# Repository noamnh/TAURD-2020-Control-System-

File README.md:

# TAURD-2020-Control-System
TAU - formula student control system design
this control system include two nucleo micro controllers board which communicate each other via can
and transmit data between section and areas of the formula vehicle.
the main purpose is to transmit the pedal data from the front micro controller to the rear micro controller
the rear micro controller controls the thorttle position.
for making a robust and reliable a pcb board was design and prduced via eagle pcb cad.

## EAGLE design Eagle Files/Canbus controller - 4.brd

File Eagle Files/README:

This is the files of the pcb printed for this project

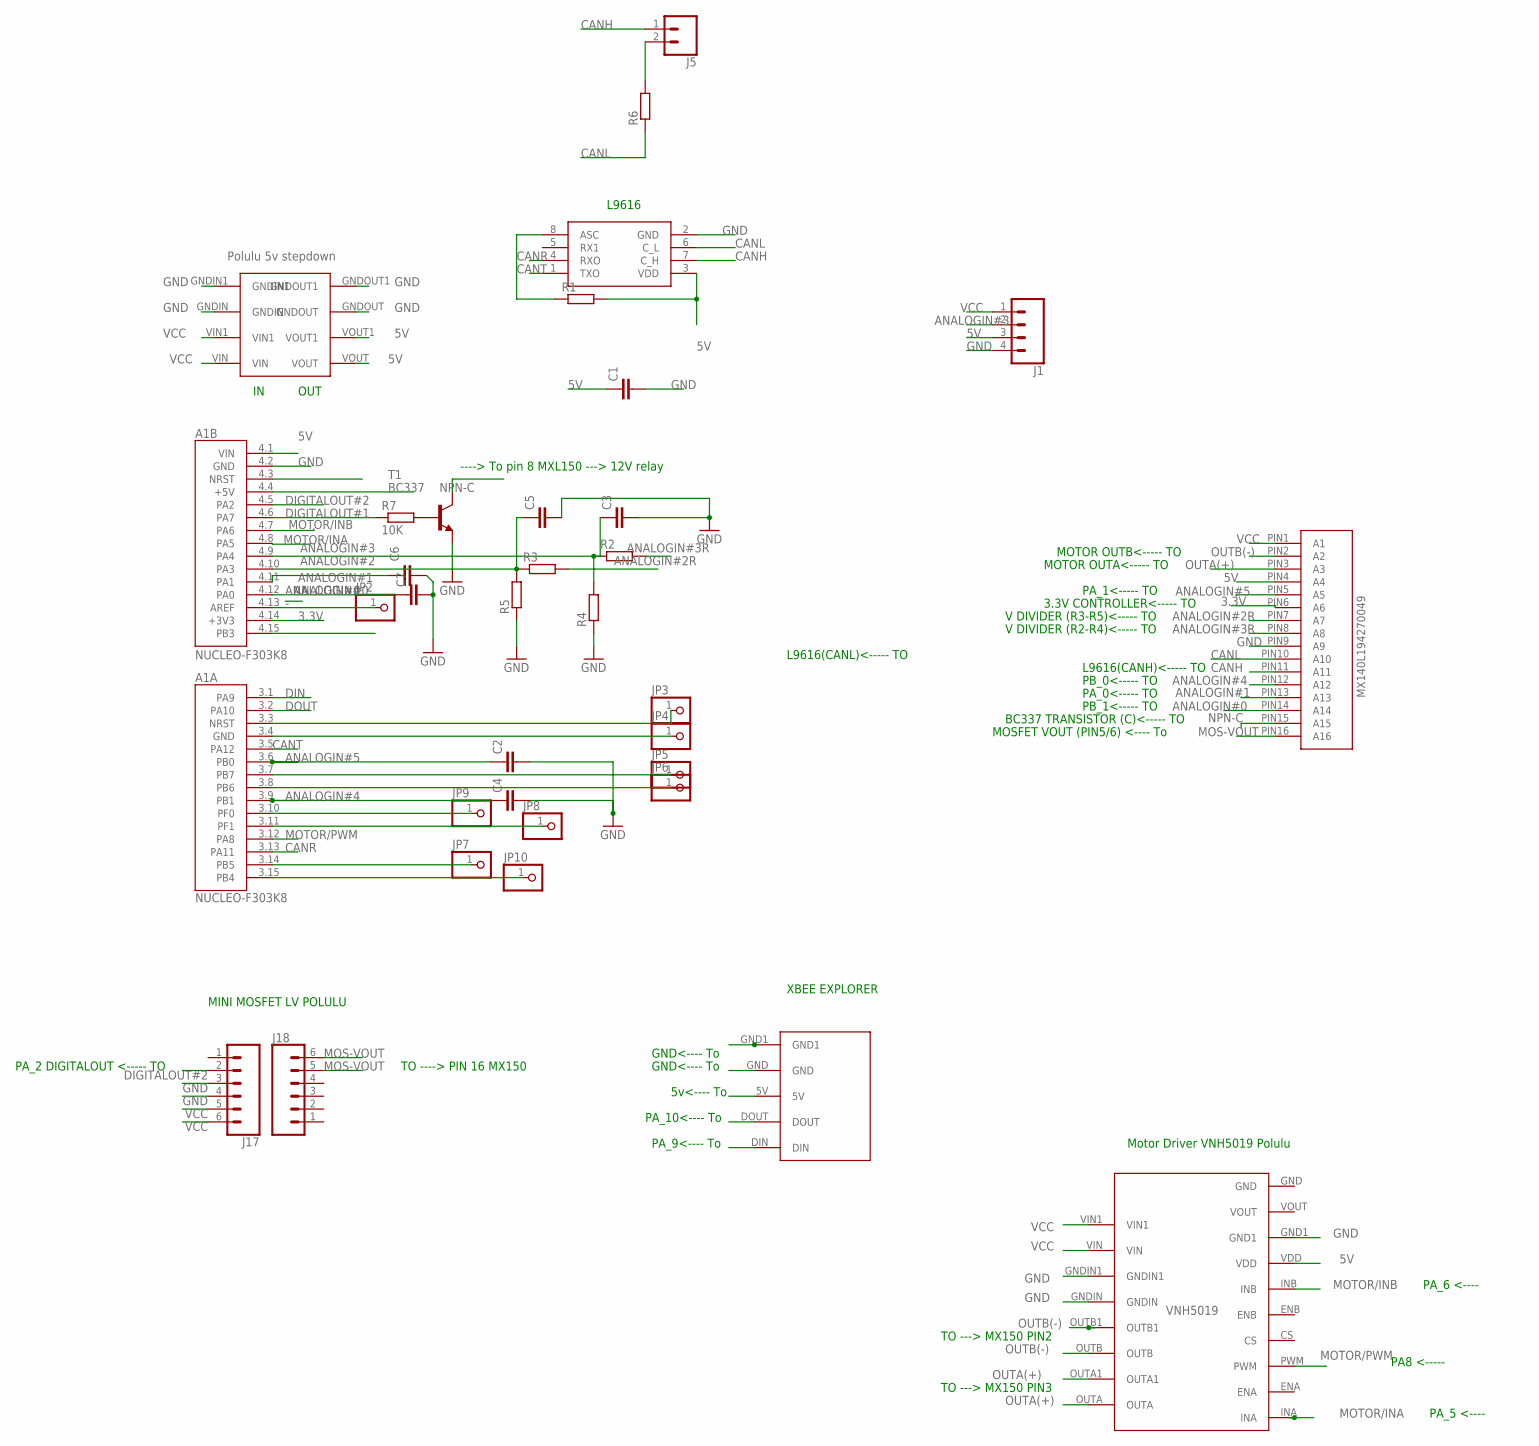
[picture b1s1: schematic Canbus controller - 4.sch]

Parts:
A1: NUCLEO-F303K8; MODULE_NUCLEO-F303K8
C1: C2,5-3; C2.5-3
C2, C3, C4, C5, C6, C7: C-EUC0805; C0805
J1: CONN_04POLAR; MOLEX-1X4
J5: CONN_02; 1X02
J17, J18: CONN_06NO_SILK_FEMALE_PTH; 1X06_NO_SILK
JP2, JP3, JP4, JP5, JP6, JP7, JP8, JP9, JP10: PINHD-1X1; 1X01
R1, R2, R3, R4, R5, R6: R-EU_0207/7; 0207/7
R7: 10K; 0207/7
T1: BC337; TO92
U$1: L9616; SO8
U$2: MX140L-194270049; MX150L-194270049
U$3: XBEEEXPLORER; XBEEREGULATED
U$4: VNH5019
U$5: 5VSTEPDOWN

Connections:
3.3V: A1.4.14 (+3V3), U$2.PIN6 (A6)
5V: A1.4.1 (VIN), C1.1, J1.3, R1.2, U$1.3 (VDD), U$2.PIN4 (A4), U$3.5V, U$4.VDD, U$5.VOUT, U$5.VOUT1
-: A1.4.13 (AREF), JP2.1
ANALOGIN#0: A1.4.12 (PA0), C7.1, U$2.PIN14 (A14)
ANALOGIN#1: A1.4.11 (PA1), C6.1, U$2.PIN13 (A13)
ANALOGIN#2: A1.4.10 (PA3), C5.1, R3.1, R5.2
ANALOGIN#2R: R3.2, U$2.PIN7 (A7)
ANALOGIN#3: A1.4.9 (PA4), C3.1, J1.2, R2.1, R4.2
ANALOGIN#3R: R2.2, U$2.PIN8 (A8)
ANALOGIN#4: A1.3.9 (PB1), C4.1, U$2.PIN12 (A12)
ANALOGIN#5: A1.3.6 (PB0), C2.1, U$2.PIN5 (A5)
CANH: J5.1, U$1.7 (C_H), U$2.PIN11 (A11)
CANL: R6.1, U$1.6 (C_L), U$2.PIN10 (A10)
CANR: A1.3.13 (PA11), U$1.4 (RXO)
CANT: A1.3.5 (PA12), U$1.1 (TXO)
DIGITALOUT#1: A1.4.6 (PA7), R7.1
DIGITALOUT#2: A1.4.5 (PA2), J17.2
DIN: A1.3.1 (PA9), U$3.DIN
DOUT: A1.3.2 (PA10), U$3.DOUT
GND: A1.4.2 (GND), C1.2, C2.2, C3.2, C4.2, C5.2, C6.2, C7.2, J1.4, J17.3, J17.4, R4.1, R5.1, T1.1 (E), U$1.2 (GND), U$2.PIN9 (A9), U$3.GND, U$3.GND1, U$4.GND1, U$4.GNDIN, U$4.GNDIN1, U$5.GNDIN, U$5.GNDIN1, U$5.GNDOUT, U$5.GNDOUT1
MOS-VOUT: J18.5, J18.6, U$2.PIN16 (A16)
MOTOR/INA: A1.4.8 (PA5), U$4.INA
MOTOR/INB: A1.4.7 (PA6), U$4.INB
MOTOR/PWM: A1.3.12 (PA8), U$4.PWM
unnamed: A1.3.3 (NRST), JP3.1
unnamed: R7.2, T1.2 (B)
unnamed: J5.2, R6.2
unnamed: R1.1, U$1.8 (ASC)
unnamed: A1.3.4 (GND), JP4.1
unnamed: A1.3.7 (PB7), JP5.1
unnamed: A1.3.8 (PB6), JP6.1
unnamed: A1.3.10 (PF0), JP9.1
unnamed: A1.3.11 (PF1), JP8.1
unnamed: A1.3.14 (PB5), JP7.1
unnamed: A1.3.15 (PB4), JP10.1
NPN-C: T1.3 (C), U$2.PIN15 (A15)
OUTA(+): U$2.PIN3 (A3), U$4.OUTA, U$4.OUTA1
OUTB(-): U$2.PIN2 (A2), U$4.OUTB, U$4.OUTB1
VCC: J1.1, J17.5, J17.6, U$2.PIN1 (A1), U$4.VIN, U$4.VIN1, U$5.VIN, U$5.VIN1

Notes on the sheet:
OUT
Motor Driver VNH5019 Polulu
PA8 <-----
PA_5 <----
PA_6 <----
MINI MOSFET LV POLULU
----> To pin 8 MXL150 ---> 12V relay
XBEE EXPLORER
PA_9<---- To
PA_10<---- To
5v<---- To
GND<---- To
MOSFET VOUT (PIN5/6) <---- To
BC337 TRANSISTOR (C)<----- TO
PB_1<----- TO
PA_0<----- TO
PB_0<----- TO
L9616(CANH)<----- TO
L9616(CANL)<----- TO
V DIVIDER (R2-R4)<----- TO
V DIVIDER (R3-R5)<----- TO
3.3V CONTROLLER<----- TO
PA_1<----- TO
MOTOR OUTA<----- TO
MOTOR OUTB<----- TO
PA_2 DIGITALOUT <----- TO
TO ----> PIN 16 MX150
TO ---> MX150 PIN3
TO ---> MX150 PIN2
L9616

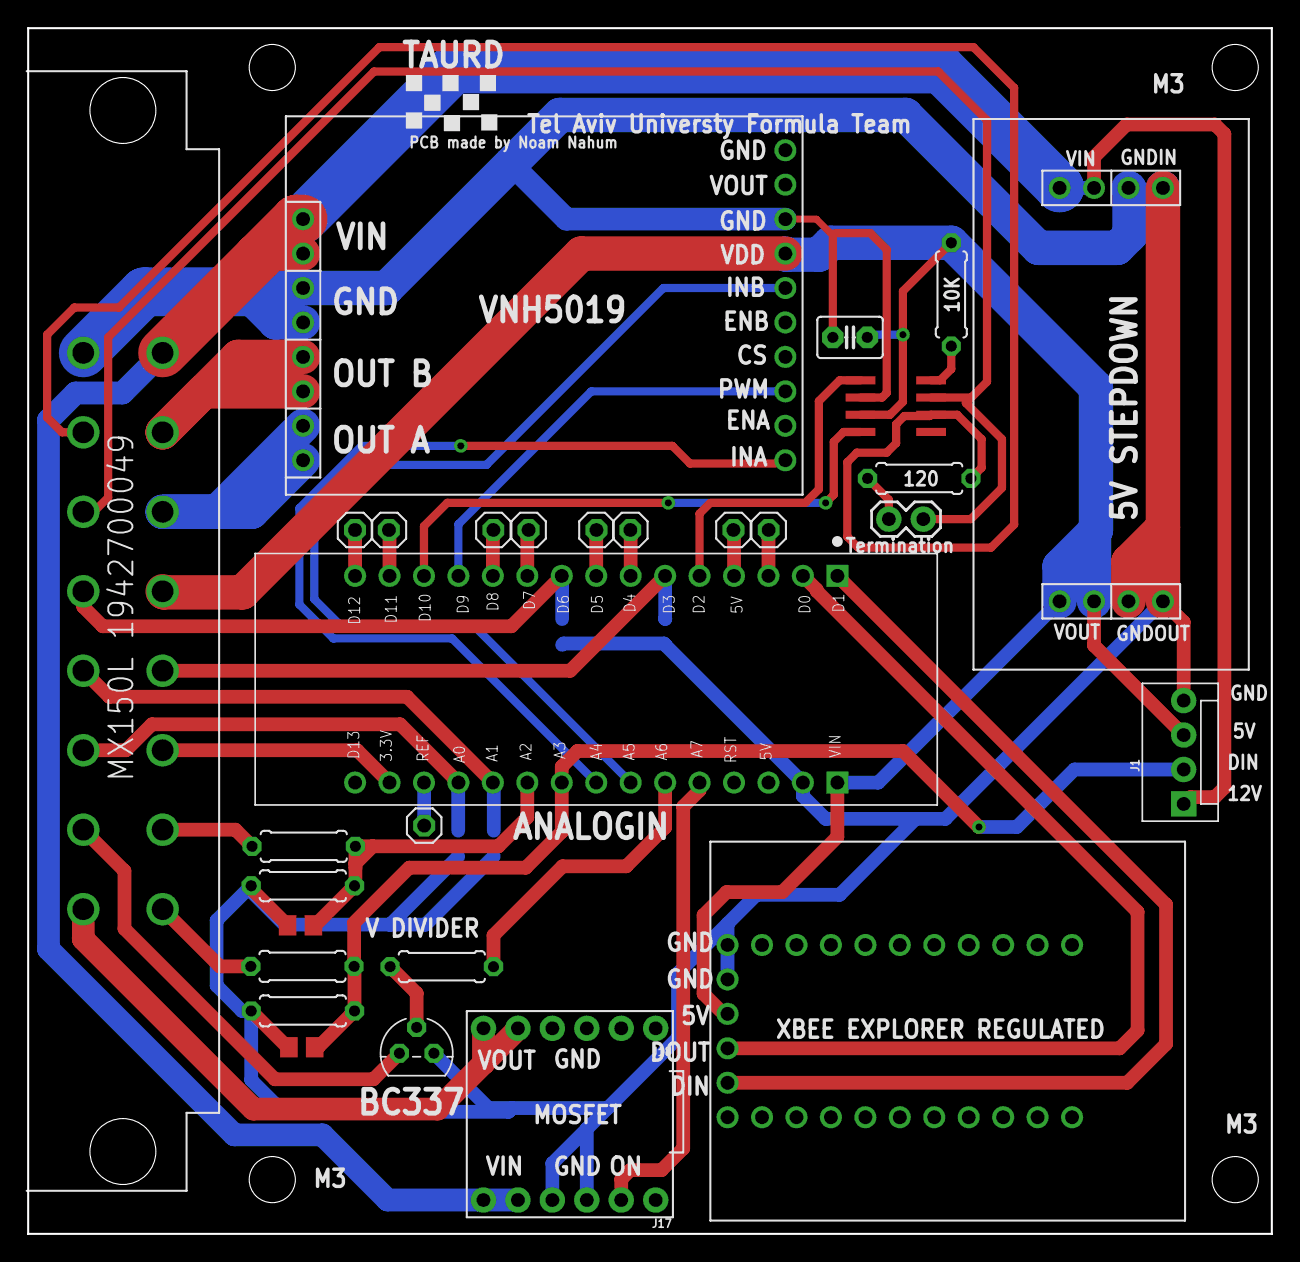
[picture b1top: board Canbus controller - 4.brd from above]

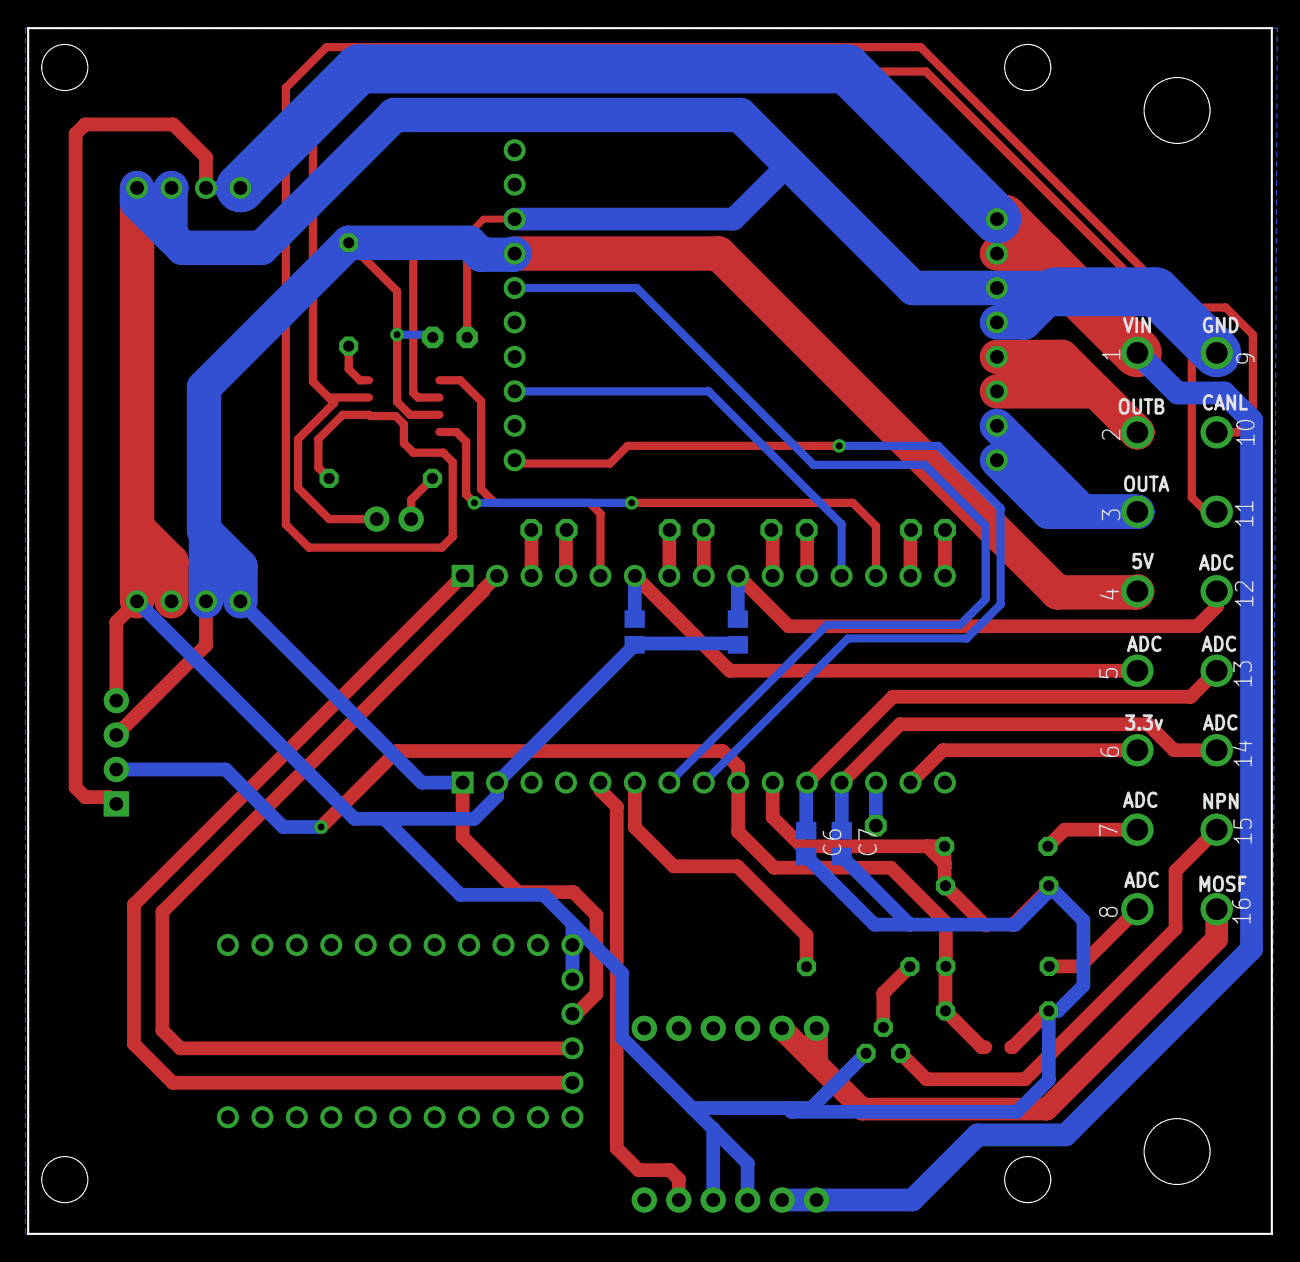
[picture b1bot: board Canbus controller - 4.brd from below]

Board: 2 copper layers, 91.7 x 88.9 mm, 34 parts (4 on the bottom side), 39 nets.

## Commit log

2020-10-31 Create src
2020-10-31 Create Rear Controller
2020-10-31 Rename Rear Controller to RearController.cpp
2020-10-31 Rename Front controller.cpp to Frontcontroller.cpp
2020-10-31 Create LICENSE
2020-10-31 Create EAGLE Files

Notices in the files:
parts and their libraries:
SparkFun-Connectors: Licensing: Creative Commons ShareAlike 4.0 International - https://creativecommons.org/licenses/by-sa/4.0
